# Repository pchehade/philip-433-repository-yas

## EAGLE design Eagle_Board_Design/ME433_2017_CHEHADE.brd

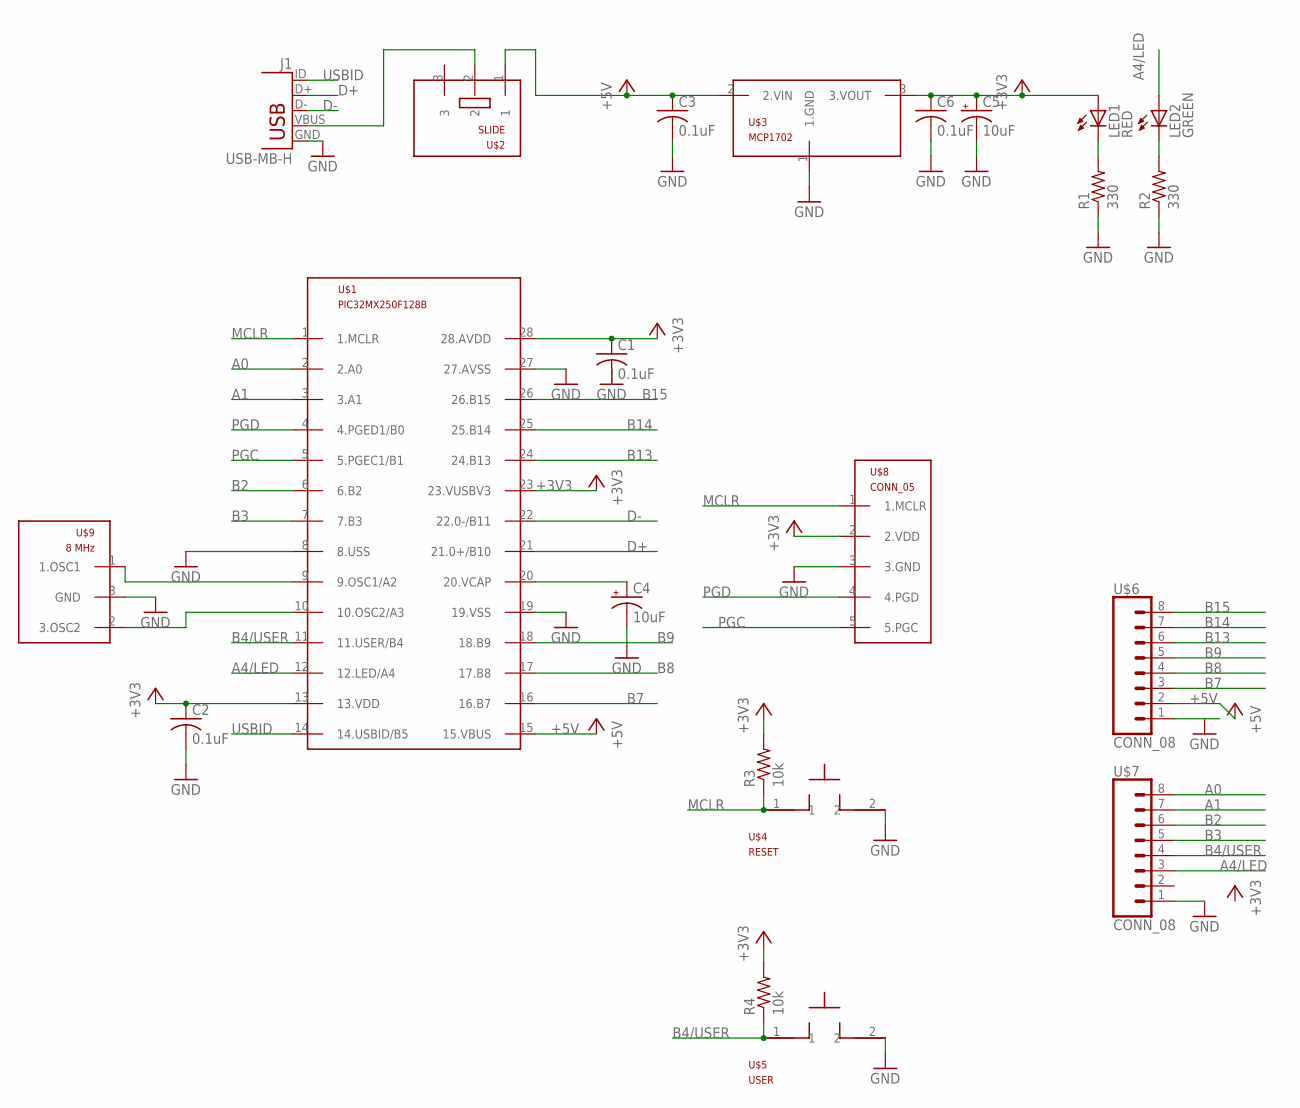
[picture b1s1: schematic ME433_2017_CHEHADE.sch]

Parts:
C1, C2, C3, C6: 0.1uF; C025-025X050
C4, C5: 10uF; B45181B
J1: USB-MB-H
LED1: RED; LED3MM
LED2: GREEN; LED3MM
R1, R2: 330; 0207/10
R3, R4: 10k; 0207/10
U$1: PIC32MX250F128B; DIL28-3
U$2: SLIDE
U$3: MCP1702; TO92
U$4: RESET; PB
U$5: USER; PB
U$6, U$7: CONN_08; 1X08
U$8: CONN_05; 1X05
U$9: 8 MHz; OSC

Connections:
+3V3: C1.1, C2.1, C5.+, C6.1, LED1.A, R3.2, R4.2, U$1.13 (13.VDD), U$1.23 (23.VUSBV3), U$1.28 (28.AVDD), U$3.3 (3.VOUT), U$8.2 (2.VDD)
+5V: C3.1, U$1.15 (15.VBUS), U$2.1, U$3.2 (2.VIN), U$6.2
A0: U$1.2 (2.A0), U$7.8
A1: U$1.3 (3.A1), U$7.7
A4/LED: LED2.A, U$1.12 (12.LED/A4), U$7.3
B2: U$1.6 (6.B2), U$7.6
B3: U$1.7 (7.B3), U$7.5
B4/USER: R4.1, U$1.11 (11.USER/B4), U$5.1, U$7.4
B7: U$1.16 (16.B7), U$6.3
B8: U$1.17 (17.B8), U$6.4
B9: U$1.18 (18.B9), U$6.5
B13: U$1.24 (24.B13), U$6.6
B14: U$1.25 (25.B14), U$6.7
B15: U$1.26 (26.B15), U$6.8
D+: J1.D+, U$1.21 (21.0+/B10)
D-: J1.D-, U$1.22 (22.0-/B11)
GND: C1.2, C2.2, C3.2, C4.-, C5.-, C6.2, J1.GND, R1.1, R2.1, U$1.8 (8.USS), U$1.19 (19.VSS), U$1.27 (27.AVSS), U$3.1 (1.GND), U$4.2, U$5.2, U$7.1, U$8.3 (3.GND), U$9.3 (GND)
MCLR: R3.1, U$1.1 (1.MCLR), U$4.1, U$8.1 (1.MCLR)
unnamed: J1.VBUS, U$2.2
unnamed: C4.+, U$1.20 (20.VCAP)
unnamed: LED1.K (C), R1.2
unnamed: U$1.9 (9.OSC1/A2), U$9.1 (1.OSC1)
unnamed: U$1.10 (10.OSC2/A3), U$9.2 (3.OSC2)
unnamed: LED2.K (C), R2.2
PGC: U$1.5 (5.PGEC1/B1), U$8.5 (5.PGC)
PGD: U$1.4 (4.PGED1/B0), U$8.4 (4.PGD)
USBID: J1.ID, U$1.14 (14.USBID/B5)

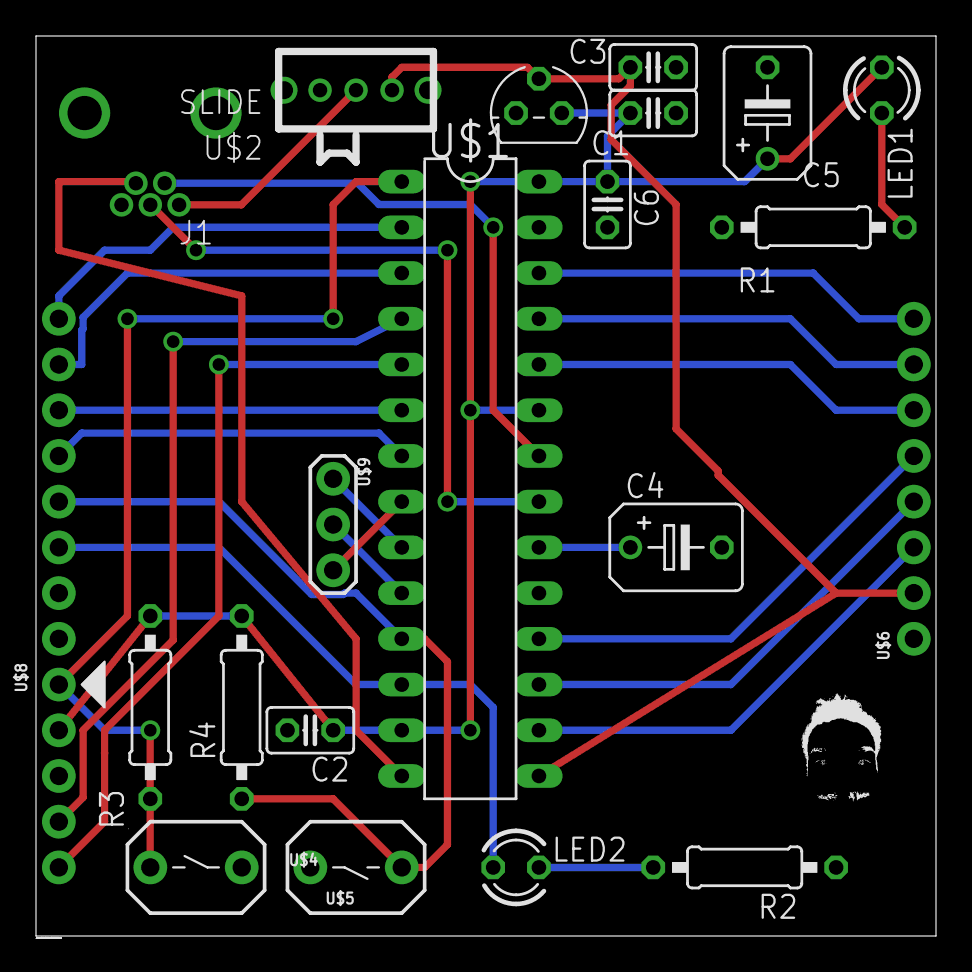
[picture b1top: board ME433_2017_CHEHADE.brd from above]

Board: 2 copper layers, 50.0 x 50.0 mm, 22 parts (1 on the bottom side), 27 nets.

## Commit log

2017-03-30 Simple Pic
    Copy and pasted simple pic to try and use it for this code
2017-03-30 Output bits
    Added output bits for LED and pushbutton
2017-03-30 LED Dimmer
    Added the LED dimmer function
2017-03-30 Push Button Switch Update
    Added function to use switch to stop light. it works!
2017-04-10 All of my files for Eagle board design
    Check it out!
2017-04-10 Files for eagle project
    .brd contains final export for Seeed. Others are design files for
    eagle.
